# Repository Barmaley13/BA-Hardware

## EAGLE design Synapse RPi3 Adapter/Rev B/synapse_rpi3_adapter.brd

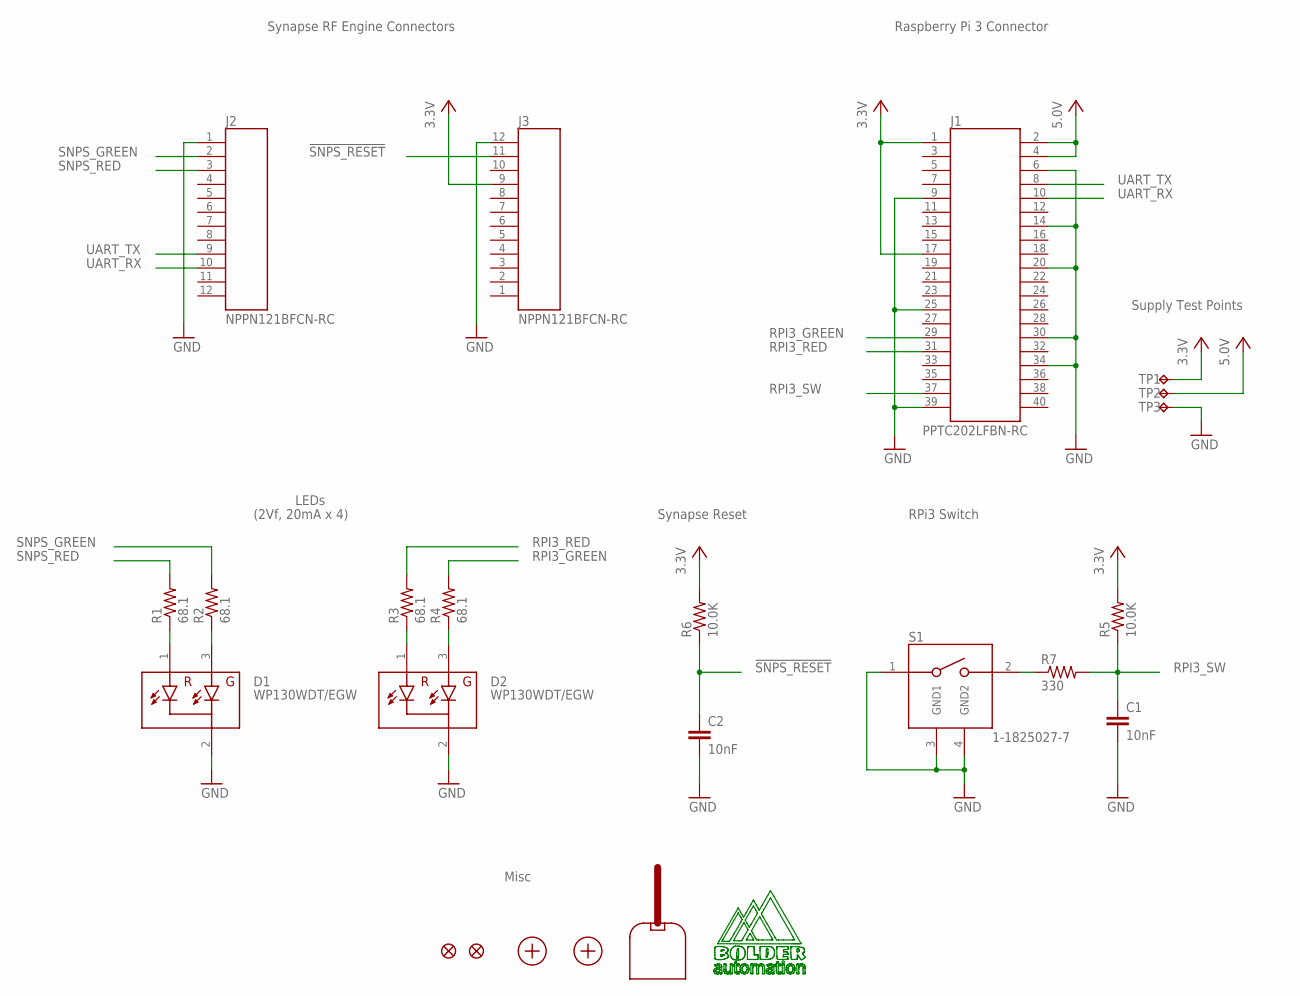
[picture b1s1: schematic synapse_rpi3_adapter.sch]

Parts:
C1, C2: 10nF; C0603
D1, D2: WP130WDT/EGW
FD1, FD2: FIDUCIALUFIDUCIAL; MICRO-FIDUCIAL
J1: PPTC202LFBN-RC
J2, J3: NPPN121BFCN-RC
MNT1, MNT2: MOUNT-HOLE-NO-PLATE5.0MM; MOUNT-HOLE-NO-PLATE-5.0MM
R1, R2, R3, R4: 68.1; R0603
R5, R6: 10.0K; R0603
R7: 330; R0603
S1: 1-1825027-7
TP1, TP2, TP3: TEST-POINT; TEST-POINT-40MILL
U$1: BA_LOGO
X1: RF200PD1

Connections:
0V: C1.2, C2.2, D1.2, D2.2, J1.6, J1.9, J1.14, J1.20, J1.25, J1.30, J1.34, J1.39, J2.1, J3.12, S1.1, S1.3 (GND1), S1.4 (GND2), TP3.1
3.3V: J1.1, J1.17, J3.9, R5.2, R6.2, TP1.1
5.0V: J1.2, J1.4, TP2.1
!SNPS_RESET: C2.1, J3.11, R6.1
unnamed: D1.1 (RED), R1.1
unnamed: D1.3 (GRN), R2.1
unnamed: D2.1 (RED), R3.1
unnamed: D2.3 (GRN), R4.1
unnamed: R7.1, S1.2
RPI3_GREEN: J1.29, R4.2
RPI3_RED: J1.31, R3.2
RPI3_SW: C1.1, J1.37, R5.1, R7.2
SNPS_GREEN: J2.2, R2.2
SNPS_RED: J2.3, R1.2
UART_RX: J1.10, J2.10
UART_TX: J1.8, J2.9

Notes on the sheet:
Synapse RF Engine Connectors
Raspberry Pi 3 Connector
(2Vf, 20mA x 4)
LEDs
RPi3 Switch
Synapse Reset
Misc
Supply Test Points

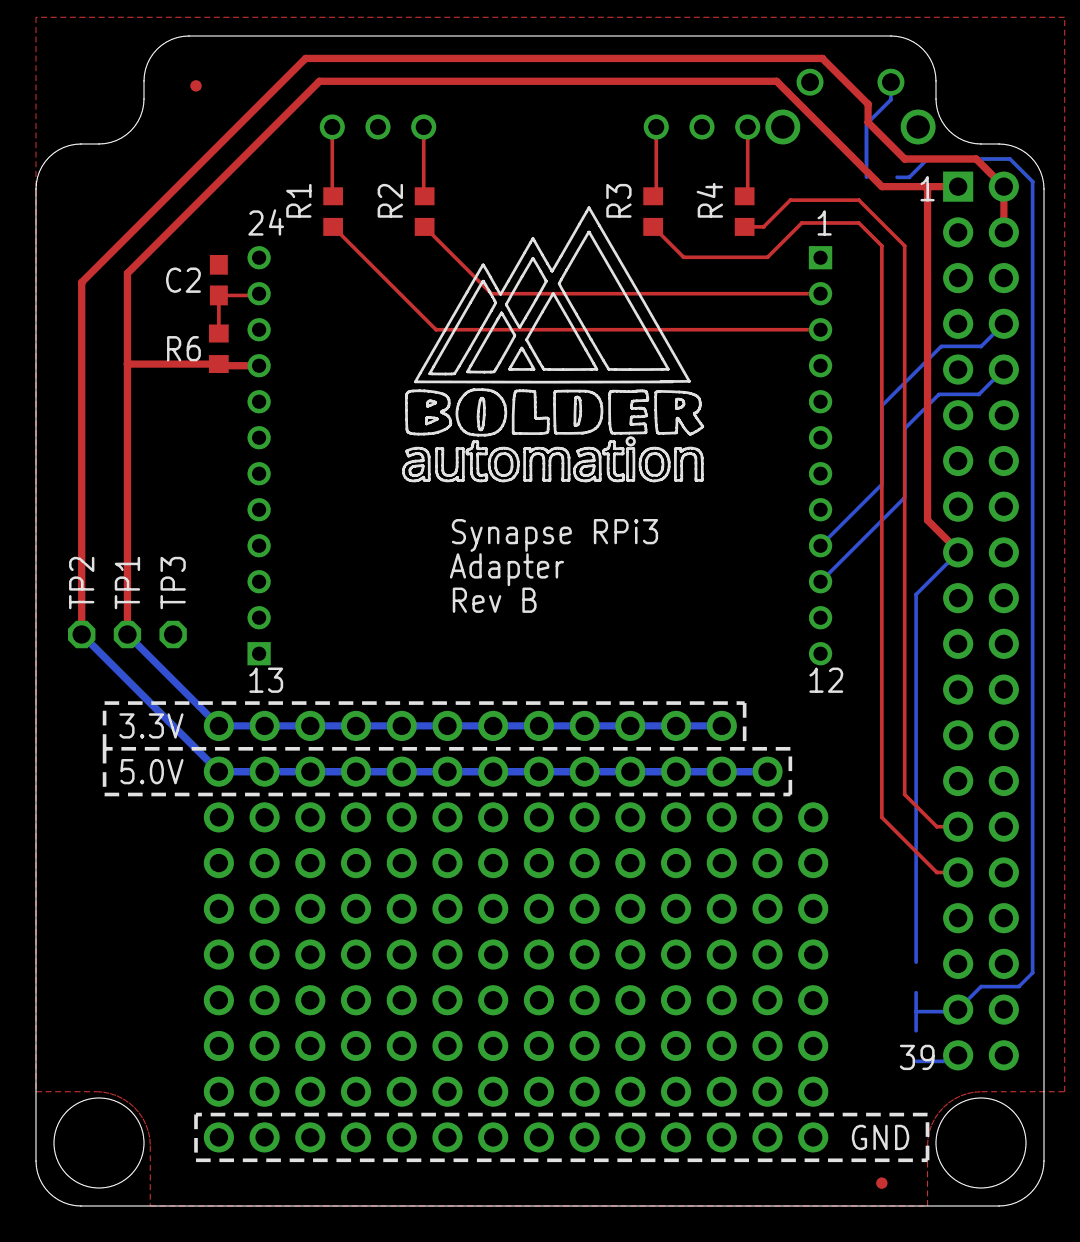
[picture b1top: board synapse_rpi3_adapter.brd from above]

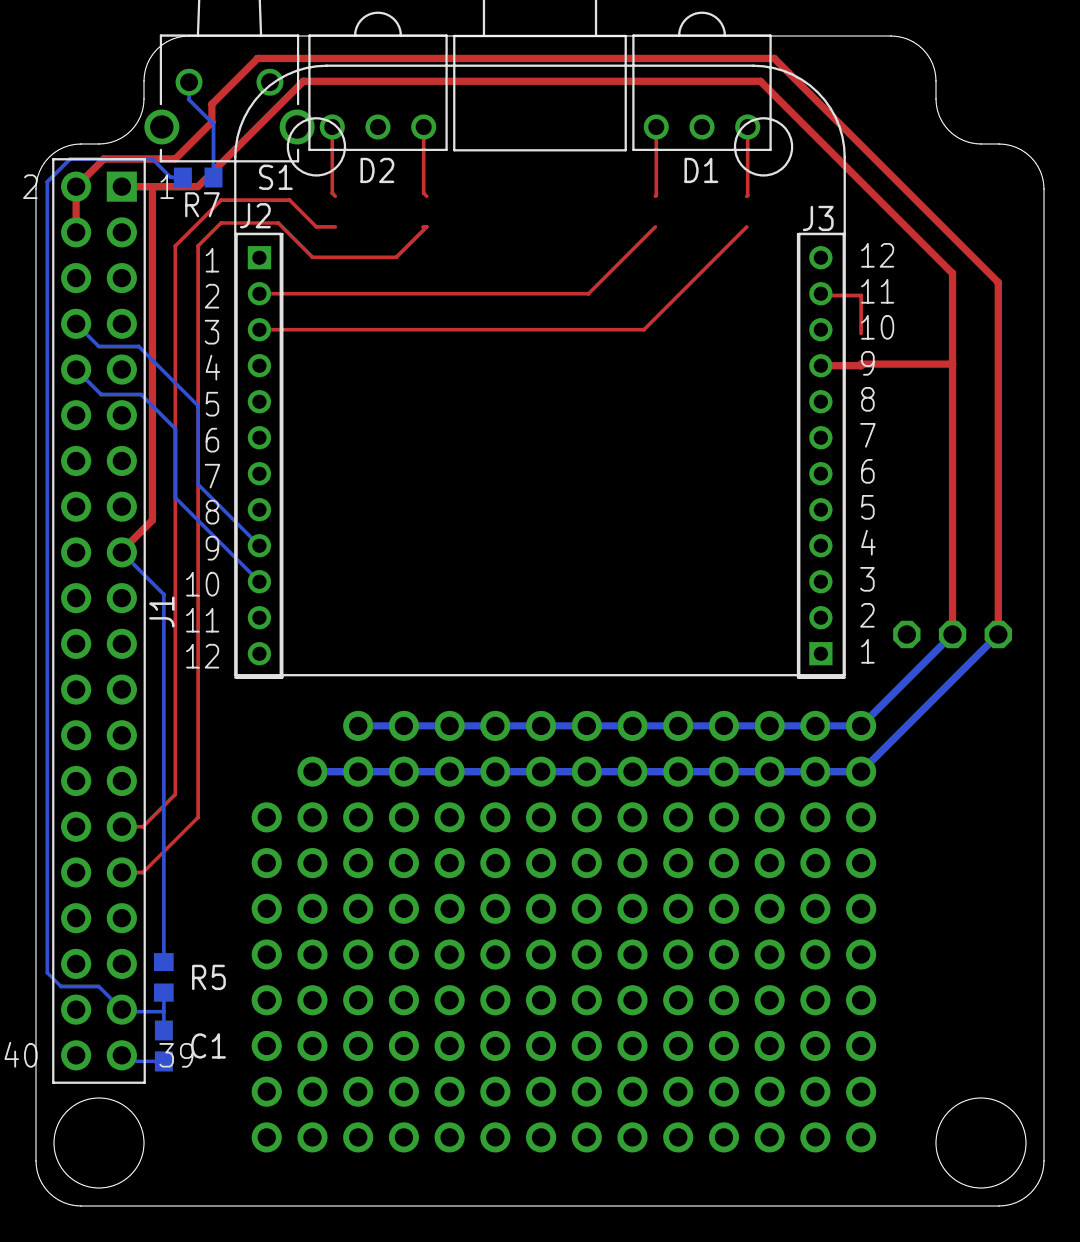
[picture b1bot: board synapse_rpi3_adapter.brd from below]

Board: 2 copper layers, 56.0 x 65.0 mm, 24 parts (10 on the bottom side), 16 nets.

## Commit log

2016-11-10 :lollipop: Added .gitattributes & .gitignore files
2016-11-10 Adding Libraries 1
2016-11-10 Synapse RPi3 Adapter Schematic 1
2016-11-11 Synapse RPi3 Adapter Schematic 2
2016-11-12 Synapse RPi3 Layout 1
2016-11-12 Synapse RPi3 BOM 1
2016-11-18 Adding Libraries 2
2016-11-19 Adding 4 layer dru and cam 1
2016-11-29 Adding Mechanical Plate 1
2016-11-29 Adding Mechanical Plate 2
2016-11-29 Mechanical Plate 3
2016-11-29 Synapse RPI3 BOM 2
2016-11-29 Updating Libraries 3
2016-11-30 Updating Libraries 4
2016-12-07 Updating Libraries 5
2016-12-08 Updating Libraries 6
2016-12-10 Updating libraries 7
2016-12-13 Updating libraries 8
2016-12-14 Updating Libraries 9
2016-12-14 Updating Libraries 10
2016-12-15 Updating Libraries 11
2016-12-19 Synapse RPi3 Rev. B 1
2016-12-19 Synapse RPi3 Rev. B 2
2016-12-19 Synapse RPi3 Rev. B 3
2016-12-20 Updating Libraries 12
2017-01-02 Updating Libraries 13
2017-01-02 Updating Libraries 14
2017-01-02 Updating Libraries 15
2017-01-03 Updating Libraries 16
2017-01-03 Updating Libraries 17
2017-01-05 Updating Libraries 18
2017-01-07 Updating Libraries 19
2017-01-11 Updating Libraries 20
2017-01-26 Moving Libraries to separate repo
2017-02-03 Generating DXF for the front plate sticker 1
2017-05-17 Updating License
